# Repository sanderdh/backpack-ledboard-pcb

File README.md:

## Introduction

My company gave a backpack with an LED panel inside it for Christmas. 
I didnt like the software that came with it so I made my own pcb to mount and ESP32 and two wii nunchucks and an accelerometer/gyro at the location of the driver pcb that came with the panel.

## Features

- Fits on the panel in the original location
- Has support for a NodeMCU ESP32 Board
- Has support for a MPU-6050 accelerometer/gyro board
- 5V/GND input pins
- 3V3/GND output pins

## PCB

## Demo

## License

The MIT License (MIT)

Permission is hereby granted, free of charge, to any person obtaining a copy
of this software and associated documentation files (the "Software"), to deal
in the Software without restriction, including without limitation the rights
to use, copy, modify, merge, publish, distribute, sublicense, and/or sell
copies of the Software, and to permit persons to whom the Software is
furnished to do so, subject to the following conditions:

The above copyright notice and this permission notice shall be included in all
copies or substantial portions of the Software.

THE SOFTWARE IS PROVIDED "AS IS", WITHOUT WARRANTY OF ANY KIND, EXPRESS OR
IMPLIED, INCLUDING BUT NOT LIMITED TO THE WARRANTIES OF MERCHANTABILITY,
FITNESS FOR A PARTICULAR PURPOSE AND NONINFRINGEMENT. IN NO EVENT SHALL THE
AUTHORS OR COPYRIGHT HOLDERS BE LIABLE FOR ANY CLAIM, DAMAGES OR OTHER
LIABILITY, WHETHER IN AN ACTION OF CONTRACT, TORT OR OTHERWISE, ARISING FROM,
OUT OF OR IN CONNECTION WITH THE SOFTWARE OR THE USE OR OTHER DEALINGS IN THE
SOFTWARE.

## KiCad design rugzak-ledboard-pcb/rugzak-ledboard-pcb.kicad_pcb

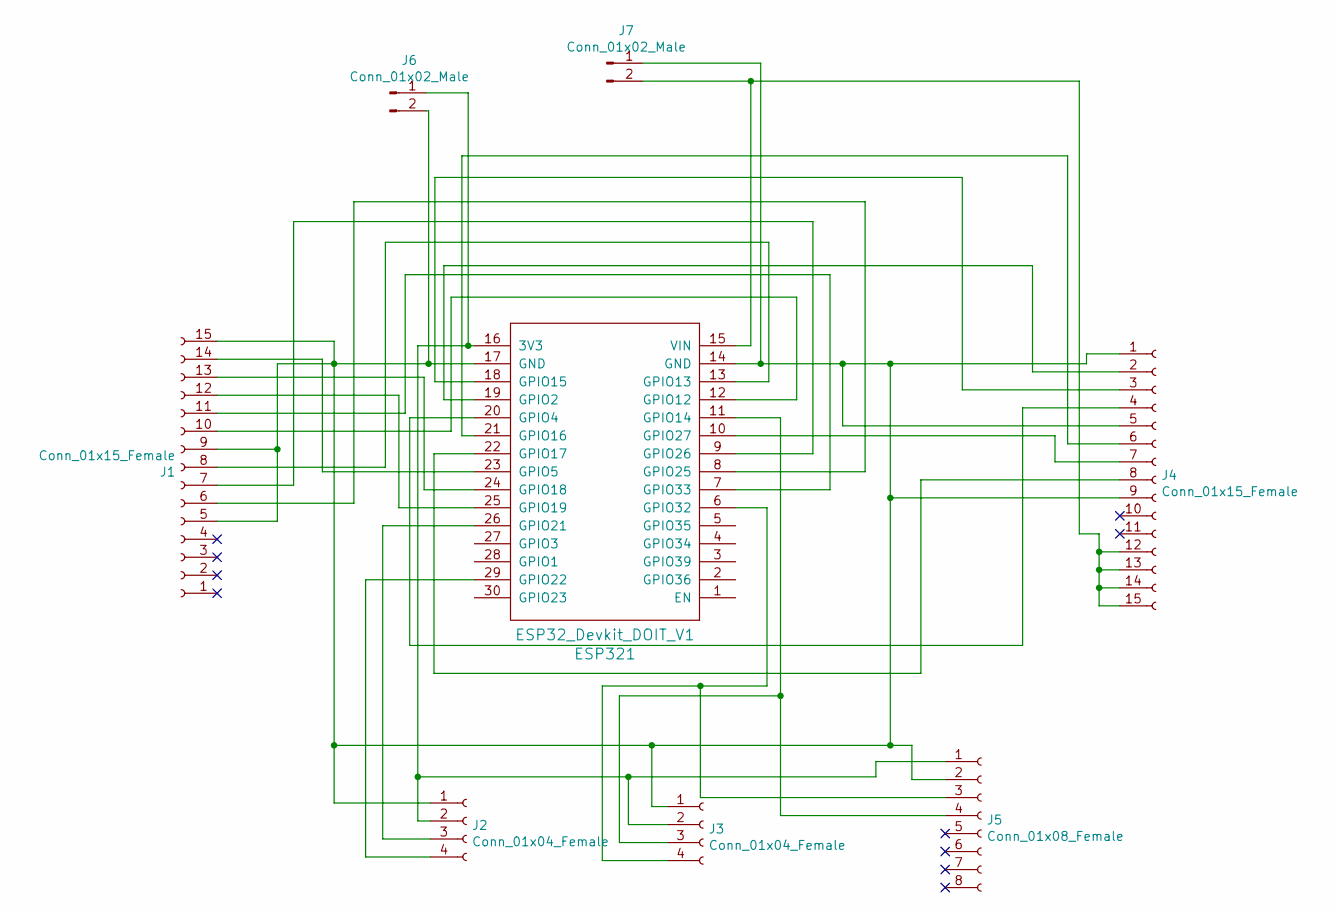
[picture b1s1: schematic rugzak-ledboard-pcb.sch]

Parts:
ESP321: ESP32_Devkit_DOIT_V1
J1, J4: Conn_01x15_Female; PinSocket_1x15_P2.54mm_Vertical
J2, J3: Conn_01x04_Female; PinSocket_1x04_P2.54mm_Vertical
J5: Conn_01x08_Female; PinSocket_1x08_P2.54mm_Vertical
J6, J7: Conn_01x02_Male; PinHeader_1x02_P2.54mm_Vertical

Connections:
unnamed: ESP321.6 (GPIO32), J3.4, J5.3
unnamed: ESP321.7 (GPIO33), J1.11
unnamed: ESP321.8 (GPIO25), J1.6
unnamed: ESP321.9 (GPIO26), J1.7
unnamed: ESP321.10 (GPIO27), J4.7
unnamed: ESP321.11 (GPIO14), J3.3, J5.4
unnamed: ESP321.12 (GPIO12), J1.10
unnamed: ESP321.13 (GPIO13), J1.8
unnamed: ESP321.14 (GND), ESP321.17 (GND), J1.5, J1.9, J1.15, J2.1, J3.1, J4.1, J4.5, J4.9, J5.2, J6.2, J7.1
unnamed: ESP321.15 (VIN), J4.12, J4.13, J4.14, J4.15, J7.2
unnamed: ESP321.16 (3V3), J2.2, J3.2, J5.1, J6.1
unnamed: ESP321.18 (GPIO15), J4.3
unnamed: ESP321.19 (GPIO2), J4.2
unnamed: ESP321.20 (GPIO4), J4.4
unnamed: ESP321.21 (GPIO16), J4.6
unnamed: ESP321.22 (GPIO17), J4.8
unnamed: ESP321.23 (GPIO5), J1.14
unnamed: ESP321.24 (GPIO18), J1.13
unnamed: ESP321.25 (GPIO19), J1.12
unnamed: ESP321.26 (GPIO21), J2.3
unnamed: ESP321.29 (GPIO22), J2.4

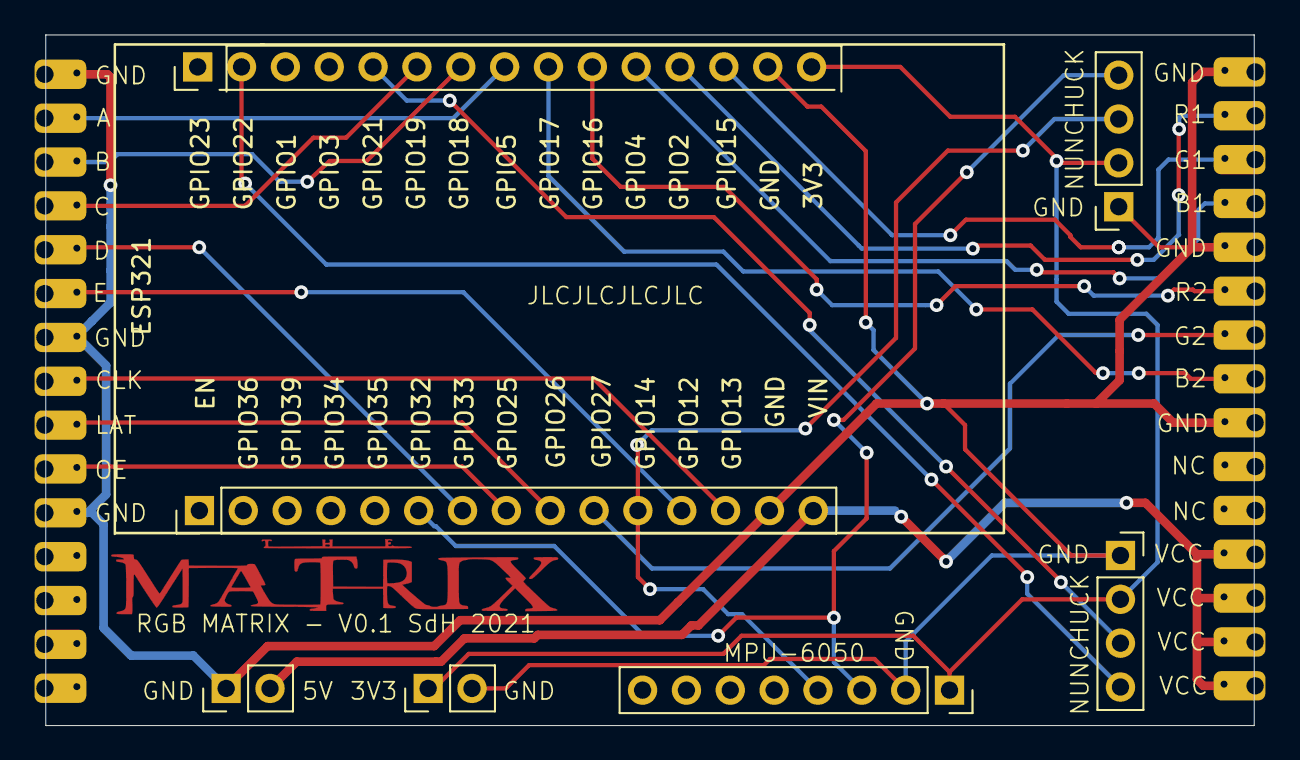
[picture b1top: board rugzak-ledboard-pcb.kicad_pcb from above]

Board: 2 copper layers, 70.0 x 40.0 mm, 8 parts (0 on the bottom side), 21 nets.

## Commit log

2021-02-11 Add demo videos
